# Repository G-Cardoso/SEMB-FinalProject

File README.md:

# SEMB-FinalProject
Projeto final da disciplina de Sistemas Embarcados - UFU

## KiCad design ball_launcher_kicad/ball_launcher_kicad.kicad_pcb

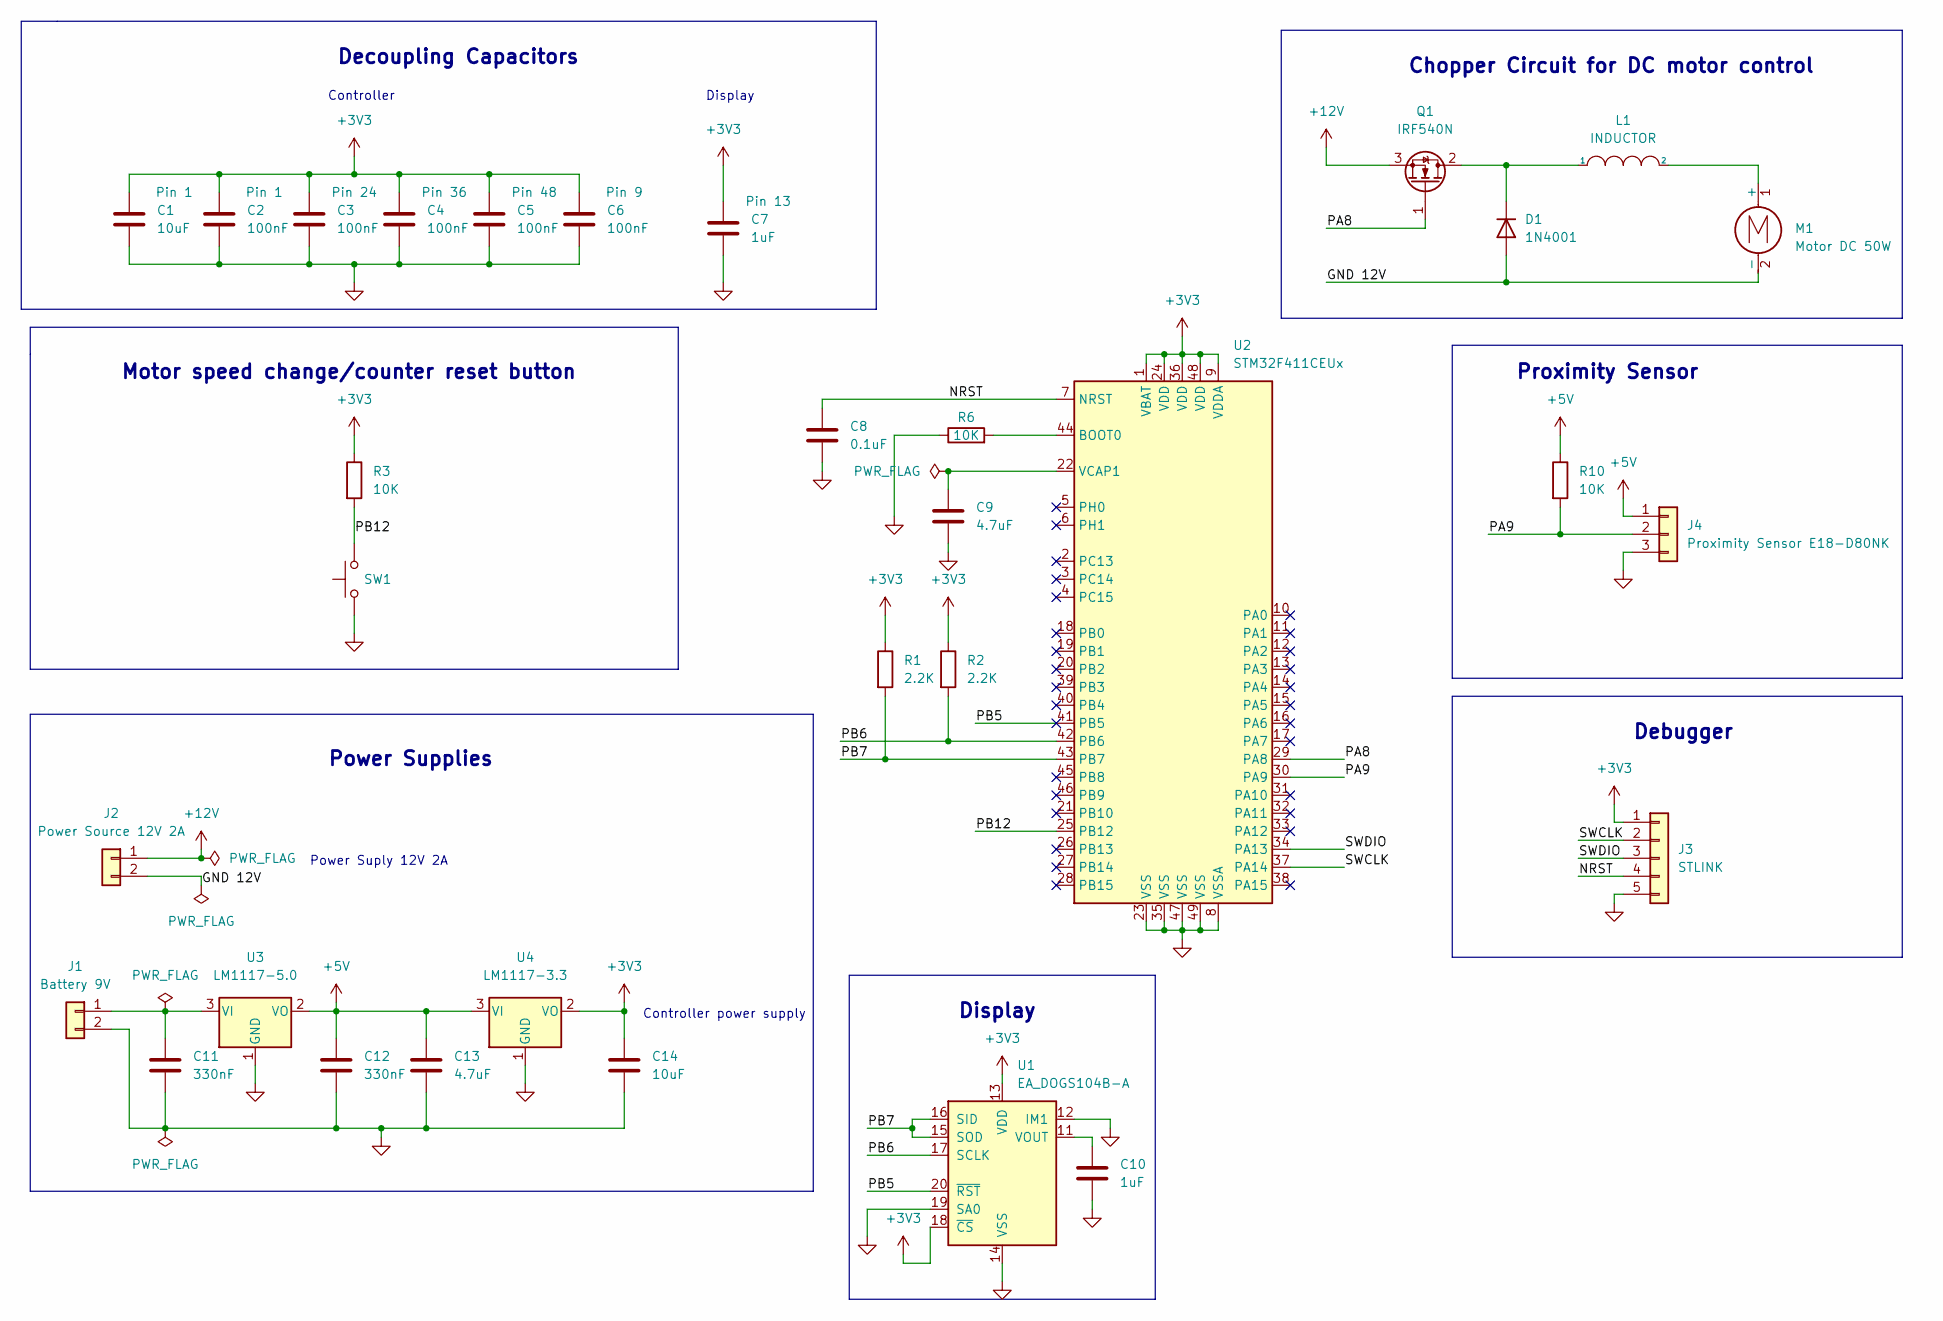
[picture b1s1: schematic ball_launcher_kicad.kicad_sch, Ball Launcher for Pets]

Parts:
C1, C14: 10uF; C_1206_3216Metric
C2, C3, C4, C5, C6: 100nF; C_0805_2012Metric
C7, C10: 1uF; C_1206_3216Metric
C8: 0.1uF; C_0805_2012Metric
C9: 4.7uF; C_0805_2012Metric
C11, C12: 330nF; C_0805_2012Metric
C13: 4.7uF; C_1206_3216Metric
D1: 1N4001; D_DO-41_SOD81_P10.16mm_Horizontal
J1: Battery 9V; BatteryHolder_Eagle_12BH611-GR
J2: Power Source 12V 2A; TerminalBlock_Phoenix_MKDS-1,5-2-5.08_1x02_P5.08mm_Horizont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
J3: STLINK; PinHeader_1x05_P2.54mm_Vertical
J4: Proximity Sensor E18-D80NK; TerminalBlock_Phoenix_MKDS-1,5-3-5.08_1x03_P5.08mm_Horizont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
L1: INDUCTOR; L_SigTra_SC3316F
M1: Motor DC 50W; TerminalBlock_Phoenix_MKDS-1,5-2-5.08_1x02_P5.08mm_Horizont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
Q1: IRF540N; TO-220-3_Vertical
R1, R2: 2.2K; R_0805_2012Metric
R3, R6, R10: 10K; R_0805_2012Metric
SW1: Button; SW_SPST_B3S-1000
U1: EA_DOGS104B-A; EA_DOGS104X-A
U2: STM32F411CEUx; QFN-48-1EP_7x7mm_P0.5mm_EP5.6x5.6mm
U3: LM1117-5.0; PinSocket_1x03_P2.54mm_Vertical
U4: LM1117-3.3; PinSocket_1x03_P2.54mm_Vertical

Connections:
+3V3: C1.1, C2.1, C3.1, C4.1, C5.1, C6.1, C7.1, C14.1, J3.1, R1.1, R2.1, R3.1, U1.13 (VDD), U1.18 (~CS), U2.1 (VBAT), U2.9 (VDDA), U2.24 (VDD), U2.36 (VDD), U2.48 (VDD), U4.2 (VO)
+5V: C12.1, C13.1, J4.1, R10.1, U3.2 (VO), U4.3 (VI)
+12V: J2.1, Q1.3 (S)
/GND 12V: D1.2 (A), J2.2, M1.2 (-)
/NRST: C8.1, J3.4, U2.7 (NRST)
/PA8: Q1.1 (G), U2.29 (PA8)
/PA9: J4.2, R10.2, U2.30 (PA9)
/PB5: U1.20 (~RST), U2.41 (PB5)
/PB6: R2.2, U1.17 (SCLK), U2.42 (PB6)
/PB7: R1.2, U1.15 (SOD), U1.16 (SID), U2.43 (PB7)
/PB12: R3.2, SW1.2, U2.25 (PB12)
/SWCLK: J3.2, U2.37 (PA14)
/SWDIO: J3.3, U2.34 (PA13)
GND: C1.2, C2.2, C3.2, C4.2, C5.2, C6.2, C7.2, C8.2, C9.2, C10.2, C11.2, C12.2, C13.2, C14.2, J1.2, J3.5, J4.3, R6.1, SW1.1, U1.12 (IM1), U1.14 (VSS), U1.19 (SA0), U2.8 (VSSA), U2.23 (VSS), U2.35 (VSS), U2.47 (VSS), U2.49 (VSS), U3.1 (GND), U4.1 (GND)
unnamed: C9.1, U2.22 (VCAP1)
unnamed: C10.1, U1.11 (VOUT)
unnamed: C11.1, J1.1, U3.3 (VI)
unnamed: D1.1 (K), L1.1, Q1.2 (D)
unnamed: L1.2, M1.1 (+)
unnamed: R6.2, U2.44 (BOOT0)

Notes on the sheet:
Chopper Circuit for DC motor control
Power Supplies
Motor speed change/counter reset button
Controller power supply
Display
Decoupling Capacitors
Controller
Proximity Sensor
Debugger
Power Suply 12V 2A

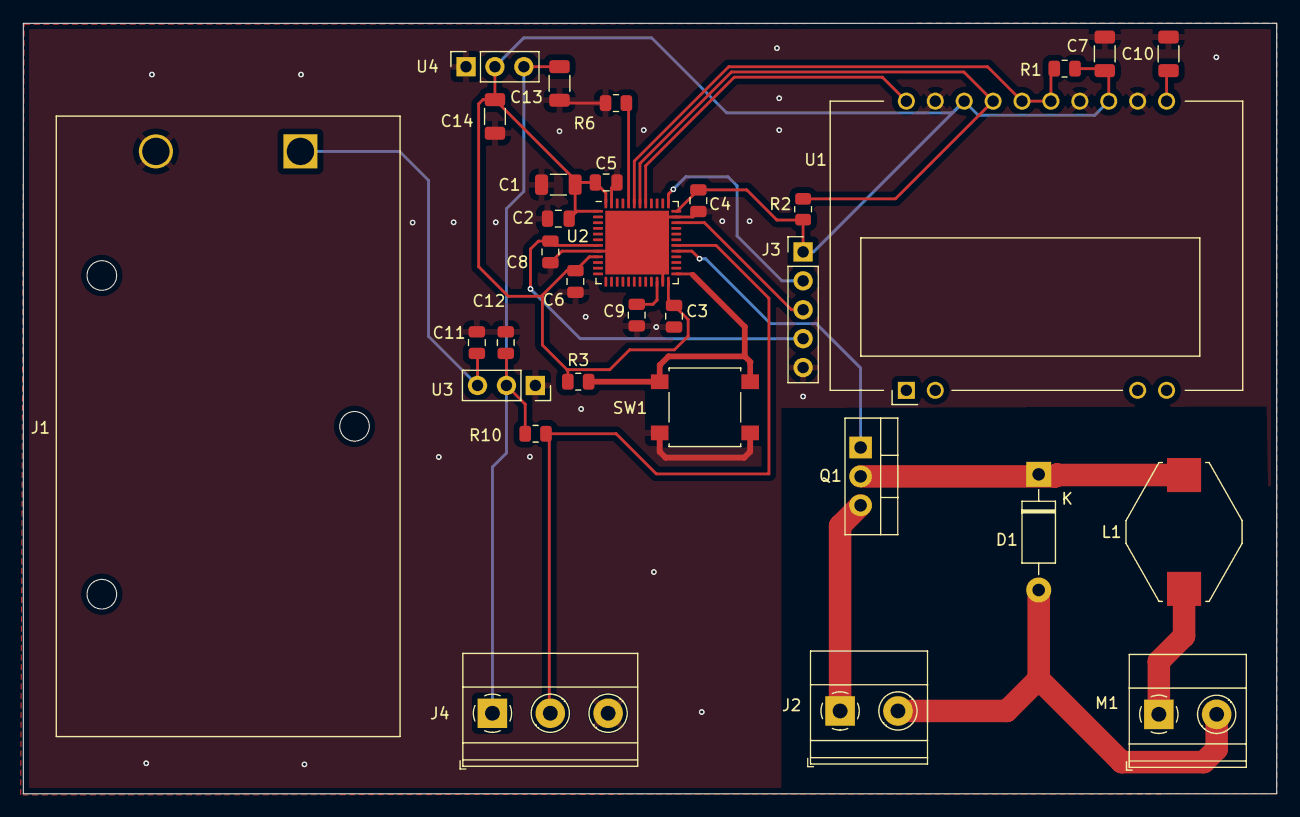
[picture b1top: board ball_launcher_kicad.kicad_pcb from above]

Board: 2 copper layers, 110.1 x 67.7 mm, 32 parts (0 on the bottom side), 20 nets.

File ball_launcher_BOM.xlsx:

Source: | /home/scdk/Dropbox/UFU/10_Periodo/Sistemas Embarcados/Projeto Final/ball_launch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
Date: | 44962.46650462963
Tool: | Eeschema 6.0.11-2627ca5db0~126~ubuntu22.04.1
Generator: | /usr/share/kicad/plugins/bom_csv_grouped_by_value.py
Component Count: | 32.0
Collated Components
Item | Qty | Reference(s) | Value | LibPart | Footprint | Datasheet | Manufacturer part number | Mouser part number
1.0 | 2.0 | C1, C14 | 10uF | Device:C | Capacitor_SMD:C_1206_3216Metric | ~ | C3216X6S2A106K16 | 810-C3216X6S2A106K16
2.0 | 5.0 | C2, C3, C4, C5, C6 | 100nF | Device:C | Capacitor_SMD:C_0805_2012Metric | ~ | C0805C104K5RAC7411 | 80-C0805C104K5RAC7411
3.0 | 2.0 | C7, C10 | 1uF | Device:C | Capacitor_SMD:C_1206_3216Metric | ~ | C1206C105K3NAUTO | 80-C1206C105K3NAUTO
4.0 | 1.0 | C8 | 0.1uF | Device:C | Capacitor_SMD:C_0805_2012Metric | ~ | C0805C104K5RAC7411 | 80-C0805C104K5RAC7411
5.0 | 1.0 | C9 | 4.7uF | Device:C | Capacitor_SMD:C_0805_2012Metric | ~ | C2012X5R2A475K12 | 810-C2012X5R2A475K12
6.0 | 2.0 | C11, C12 | 330nF | Device:C | Capacitor_SMD:C_0805_2012Metric | ~ | C0805X334K5RACAUTO | 80-C0805X334K5RACAUTO
7.0 | 1.0 | C13 | 4.7uF | Device:C | Capacitor_SMD:C_1206_3216Metric | ~ | C1206X475K4NACAUTO | 80-C1206X475K4NACAUTO
8.0 | 1.0 | D1 | 1N4001 | Diode:1N4001 | Diode_THT:D_DO-41_SOD81_P10.16mm_Horizontal | http://www.vishay.com/docs/88503/1n4001.pdf | 1N4001 | 637-1N4001
9.0 | 1.0 | J1 | Battery 9V | Connector_Generic:Conn_01x02 | Battery:BatteryHolder_Eagle_12BH611-GR | ~ | 12BH610-GR | 12BH610-GR
10.0 | 1.0 | J2 | Power Source 12V 2A | Connector_Generic:Conn_01x02 | TerminalBlock_Phoenix:TerminalBlock_Phoenix_MKDS-1,5-2-5.08_1x02_P5.08mm_Horizo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 | ~ | 1711725.0 | 651-1711725
11.0 | 1.0 | J3 | STLINK | Connector_Generic:Conn_01x05 | Connector_PinHeader_2.54mm:PinHeader_1x05_P2.54mm_Vertical | ~ | 3-644456-5 | 571-3-644456-5
12.0 | 1.0 | J4 | Proximity Sensor E18-D80NK | Connector_Generic:Conn_01x03 | TerminalBlock_Phoenix:TerminalBlock_Phoenix_MKDS-1,5-3-5.08_1x03_P5.08mm_Horizo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 | ~ | 1714735.0 | 651-1714735
13.0 | 1.0 | L1 | INDUCTOR | pspice:INDUCTOR | Inductor_SMD:L_SigTra_SC3316F | ~ | P0850NL | 673-P0850NL
14.0 | 1.0 | M1 | Motor DC 50W | Motor:Motor_DC | TerminalBlock_Phoenix:TerminalBlock_Phoenix_MKDS-1,5-2-5.08_1x02_P5.08mm_Horizo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 | ~ | 1711725.0 | 651-1711725
15.0 | 1.0 | Q1 | IRF540N | Transistor_FET:IRF540N | Package_TO_SOT_THT:TO-220-3_Vertical | http://www.irf.com/product-info/datasheets/data/irf540n.pdf | STP40NF10L | 511-STP40NF10L
16.0 | 2.0 | R1, R2 | 2.2K | Device:R | Resistor_SMD:R_0805_2012Metric | ~ | SDR10EZPJ222 | 755-SDR10EZPJ222
17.0 | 3.0 | R3, R6, R10 | 10K | Device:R | Resistor_SMD:R_0805_2012Metric | ~ | SDR10EZPJ103 | 755-SDR10EZPJ103
18.0 | 1.0 | SW1 | Button | Switch:SW_Push | Button_Switch_SMD:SW_SPST_B3S-1000 | ~ | B3S-1000 | 653-B3S-1000
19.0 | 1.0 | U1 | EA_DOGS104B-A | Display_Graphic:EA_DOGS104B-A | Display:EA_DOGS104X-A | http://www.lcd-module.com/fileadmin/eng/pdf/doma/dogs104e.pdf | EADOGS104W-A | 790-EADOGS104W-A
20.0 | 1.0 | U2 | STM32F411CEUx | MCU_ST_STM32F4:STM32F411CEUx | Package_DFN_QFN:QFN-48-1EP_7x7mm_P0.5mm_EP5.6x5.6mm | http://www.st.com/st-web-ui/static/active/en/resource/techni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 | STM32F411CEU6 | 511-STM32F411CEU6
21.0 | 1.0 | U3 | LM1117-5.0 | Regulator_Linear:LM1117-5.0 | Connector_PinSocket_2.54mm:PinSocket_1x03_P2.54mm_Vertical | http://www.ti.com/lit/ds/symlink/lm1117.pdf | LM1117T-50/NOPB | 926-LM1117T-50/NOPB
22.0 | 1.0 | U4 | LM1117-3.3 | Regulator_Linear:LM1117-3.3 | Connector_PinSocket_2.54mm:PinSocket_1x03_P2.54mm_Vertical | http://www.ti.com/lit/ds/symlink/lm1117.pdf | LM1117SX33NOPB | 926-LM1117SX33NOPB

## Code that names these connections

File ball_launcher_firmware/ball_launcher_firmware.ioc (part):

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Mcu.Name=STM32F411C(C-E)Ux
Mcu.Package=UFQFPN48
Mcu.UserName=STM32F411CEUx
PA13.GPIOParameters=GPIO_Label
PA13.GPIO_Label=SWDIO
PA13.Mode=Serial_Wire
PA13.Signal=SYS_JTMS-SWDIO
PA14.GPIOParameters=GPIO_Label
PA14.GPIO_Label=SWCLK
PA14.Mode=Serial_Wire
PA14.Signal=SYS_JTCK-SWCLK
PA8.GPIOParameters=GPIO_Label
PA8.GPIO_Label=PWM_CHOPPER
PA8.Signal=S_TIM1_CH1
PA9.GPIOParameters=GPIO_PuPd,GPIO_Label,GPIO_ModeDefaultEXTI
PA9.GPIO_Label=PROXIMITY_SENSOR
PA9.GPIO_ModeDefaultEXTI=GPIO_MODE_IT_FALLING
PA9.GPIO_PuPd=GPIO_PULLUP
PA9.Signal=GPXTI9
PB12.GPIOParameters=GPIO_PuPd,GPIO_Label,GPIO_ModeDefaultEXTI
PB12.GPIO_Label=USER_BUTTON
PB12.GPIO_ModeDefaultEXTI=GPIO_MODE_IT_RISING_FALLING
PB12.GPIO_PuPd=GPIO_PULLUP
PB12.Signal=GPXTI12
PB5.GPIOParameters=GPIO_PuPd,GPIO_Label
PB5.GPIO_Label=DISPLAY_RESET
PB5.GPIO_PuPd=GPIO_PULLDOWN
PB5.Signal=GPIO_Output
PB6.Mode=I2C
PB6.Signal=I2C1_SCL
PB7.Mode=I2C
PB7.Signal=I2C1_SDA
RCC.HSE_VALUE=25000000
RCC.SYSCLKFreq_VALUE=16000000
board=custom

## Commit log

2023-02-05 Definição do part numbers, criação do BOM e do geber
2023-02-05 Realizadas alterações no firmware para funcionamento do botão do usuário e timers
